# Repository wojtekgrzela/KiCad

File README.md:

# KiCad

My PCB projects in KiCad
 - BodyComputer [DONE]
 - DRL_Driver [DONE]
 - GPS_Adapter [DONE]
 - Listwa_zasilajaca (Power_rail) [DONE]
 - MOSFET_Rail [DONE]
 - Plytka_Dla_Peryferiow (Peripheral_Board) [DONE]
 
 MY_ELEMENTS - Electric components' symbols and footprints from the Internet.
 
 In case you would like to use any of my projects - please contact me via e-mail: wojtekgrzela@gmail.com

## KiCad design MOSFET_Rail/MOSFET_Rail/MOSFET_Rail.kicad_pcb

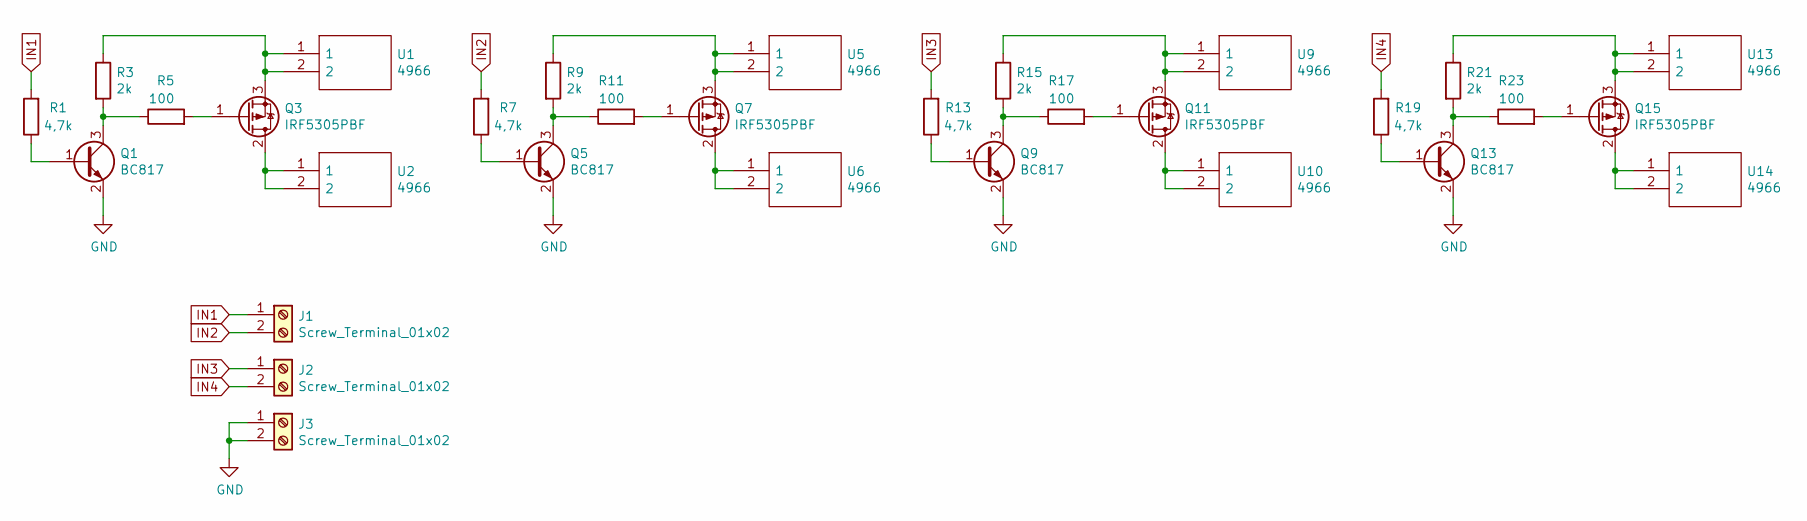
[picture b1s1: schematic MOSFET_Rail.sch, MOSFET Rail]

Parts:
J1, J2, J3: Screw_Terminal_01x02; SHDR2W99P0X500_1X2_1000X760X1000P
Q1, Q5, Q9, Q13: BC817; SOT-23
Q3, Q7, Q11, Q15: IRF5305PBF; TO-220-3_Vertical
R1, R7, R13, R19: 4,7k; R_0805_2012Metric
R3, R9, R15, R21: 2k; R_0805_2012Metric
R5, R11, R17, R23: 100; R_0805_2012Metric
U1, U2, U5, U6, U9, U10, U13, U14: 4966; Mouser Part Number 534-4966

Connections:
GND: J3.1, J3.2, Q1.2 (E), Q5.2 (E), Q9.2 (E), Q13.2 (E)
IN1: J1.1, R1.2
IN2: J1.2, R7.2
IN3: J2.1, R13.2
IN4: J2.2, R19.2
unnamed: Q1.1 (B), R1.1
unnamed: Q1.3 (C), R3.2, R5.1
unnamed: Q3.1 (G), R5.2
unnamed: Q3.2 (D), U2.1, U2.2
unnamed: Q3.3 (S), R3.1, U1.1, U1.2
unnamed: Q5.1 (B), R7.1
unnamed: Q5.3 (C), R9.2, R11.1
unnamed: Q7.1 (G), R11.2
unnamed: Q7.2 (D), U6.1, U6.2
unnamed: Q7.3 (S), R9.1, U5.1, U5.2
unnamed: Q9.1 (B), R13.1
unnamed: Q9.3 (C), R15.2, R17.1
unnamed: Q11.1 (G), R17.2
unnamed: Q11.2 (D), U10.1, U10.2
unnamed: Q11.3 (S), R15.1, U9.1, U9.2
unnamed: Q13.1 (B), R19.1
unnamed: Q13.3 (C), R21.2, R23.1
unnamed: Q15.1 (G), R23.2
unnamed: Q15.2 (D), U14.1, U14.2
unnamed: Q15.3 (S), R21.1, U13.1, U13.2

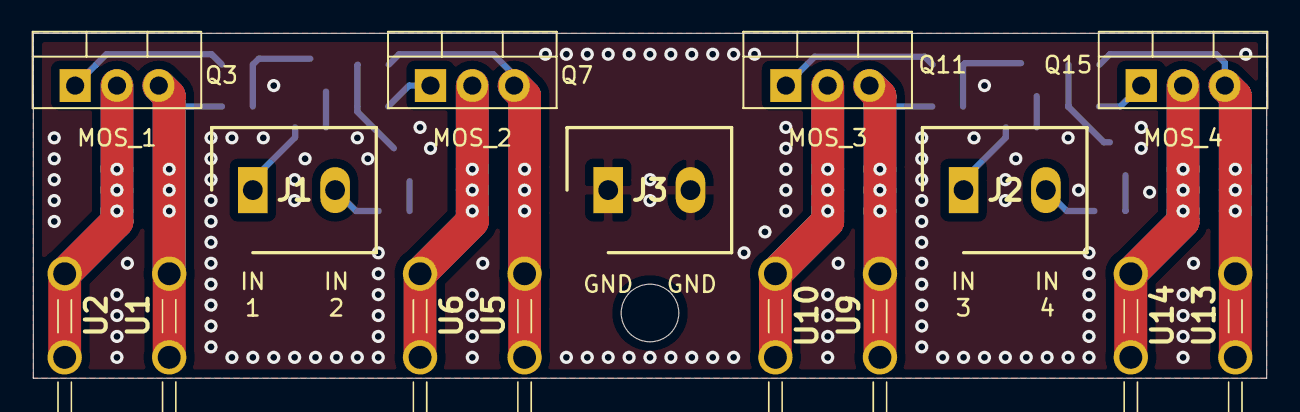
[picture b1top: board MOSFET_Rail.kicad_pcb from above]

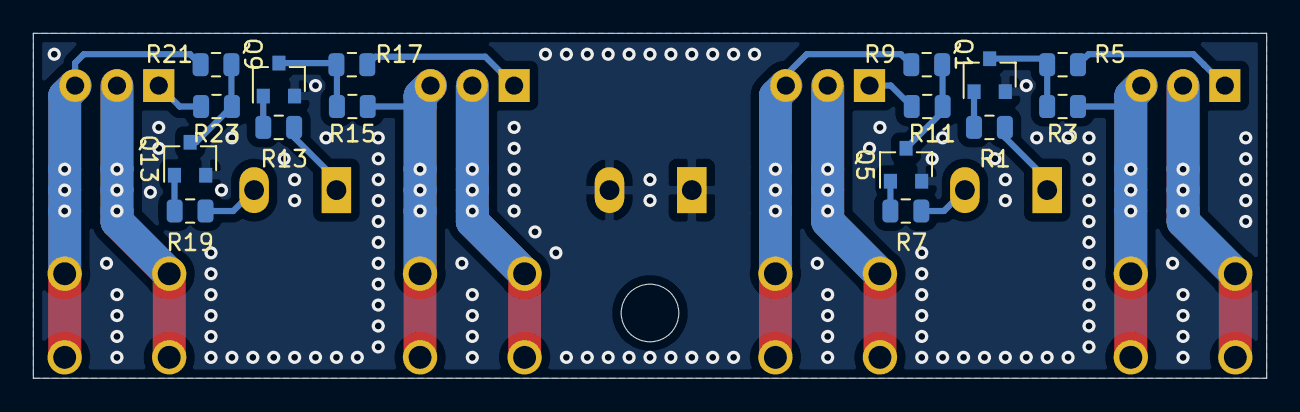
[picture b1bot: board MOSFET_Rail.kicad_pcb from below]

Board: 2 copper layers, 74.9 x 21.0 mm, 31 parts (16 on the bottom side), 25 nets.

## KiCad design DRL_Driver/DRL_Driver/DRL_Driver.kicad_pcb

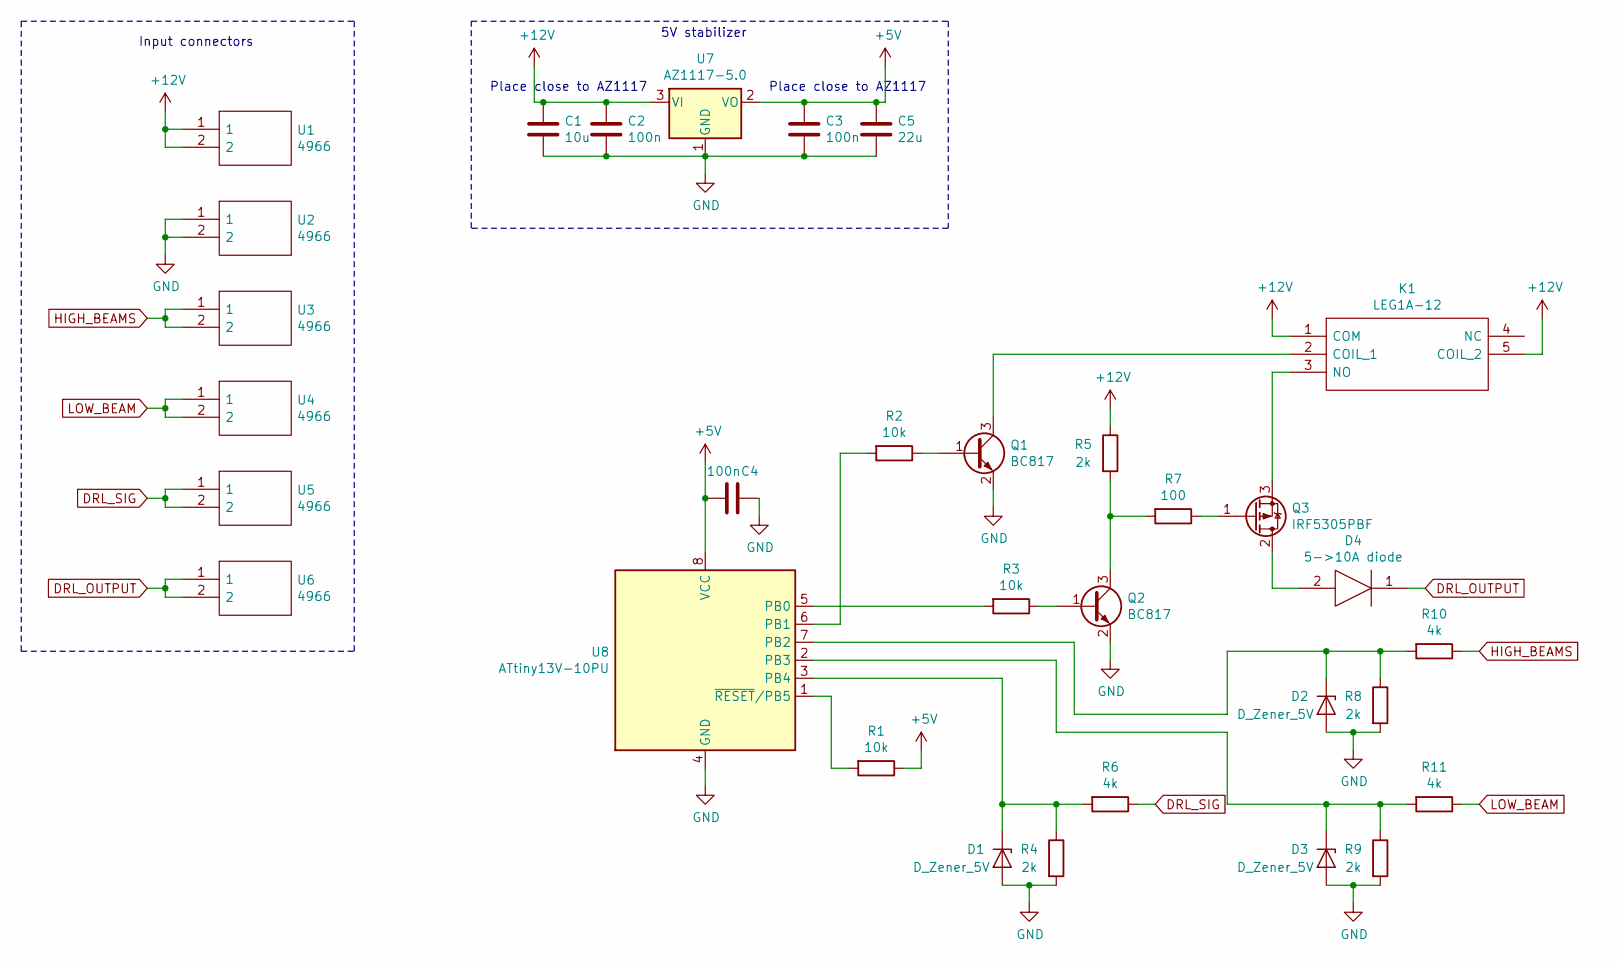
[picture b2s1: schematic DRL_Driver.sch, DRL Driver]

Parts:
C1: 10u; C_1206_3216Metric
C2, C3, C4: 100n; C_0805_2012Metric
C5: 22u; C_0805_2012Metric
D1, D2, D3: D_Zener_5V; D_SOD-323_HandSoldering
D4: 5->10A diode; DIOAD4445W127L889D889; Manufacturer_Part_Number NTE5817HC
K1: LEG1A-12; AZ943; Manufacturer_Part_Number AZ943–1CH–5D
Q1, Q2: BC817; SOT-23
Q3: IRF5305PBF; TO-220-3_Vertical
R1, R2, R3: 10k; R_0805_2012Metric
R4, R5, R8, R9: 2k; R_0805_2012Metric
R6, R10, R11: 4k; R_0805_2012Metric
R7: 100; R_0805_2012Metric
U1, U2, U3, U4, U5, U6: 4966; Mouser Part Number 534-4966
U7: AZ1117-5.0; SOT-223-3_TabPin2
U8: ATtiny13V-10PU; DIP-8_W7.62mm

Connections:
+5V: C3.1, C4.1, C5.1, R1.1, U7.2 (VO), U8.8 (VCC)
+12V: C1.1, C2.1, K1.1 (COM), K1.5 (COIL_2), R5.1, U1.1, U1.2, U7.3 (VI)
DRL_OUTPUT: D4.1, U6.1, U6.2
DRL_SIG: R6.1, U5.1, U5.2
GND: C1.2, C2.2, C3.2, C4.2, C5.2, D1.2 (A), D2.2 (A), D3.2 (A), Q1.2 (E), Q2.2 (E), R4.2, R8.2, R9.2, U2.1, U2.2, U7.1 (GND), U8.4 (GND)
HIGH_BEAMS: R10.1, U3.1, U3.2
LOW_BEAM: R11.1, U4.1, U4.2
unnamed: D1.1 (K), R4.1, R6.2, U8.3 (PB4)
unnamed: D2.1 (K), R8.1, R10.2, U8.7 (PB2)
unnamed: D3.1 (K), R9.1, R11.2, U8.2 (PB3)
unnamed: D4.2, Q3.2 (D)
unnamed: K1.2 (COIL_1), Q1.3 (C)
unnamed: K1.3 (NO), Q3.3 (S)
unnamed: Q1.1 (B), R2.1
unnamed: Q2.1 (B), R3.1
unnamed: Q2.3 (C), R5.2, R7.2
unnamed: Q3.1 (G), R7.1
unnamed: R1.2, U8.1 (~RESET~/PB5)
unnamed: R2.2, U8.6 (PB1)
unnamed: R3.2, U8.5 (PB0)

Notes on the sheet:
Place close to AZ1117
Input connectors
5V stabilizer

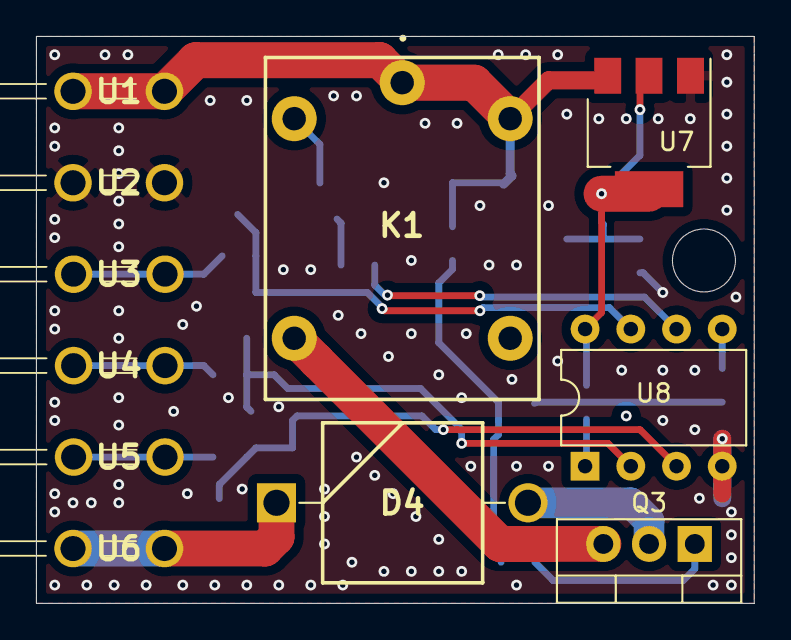
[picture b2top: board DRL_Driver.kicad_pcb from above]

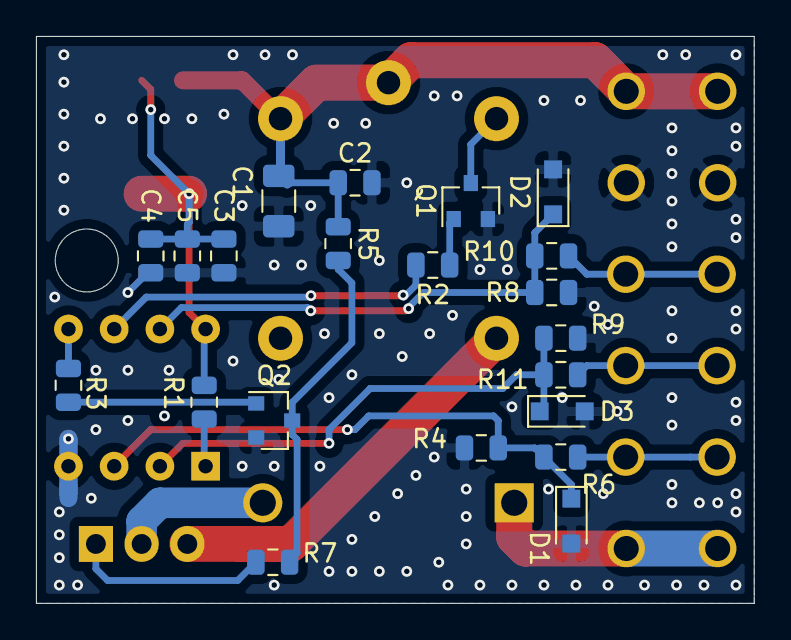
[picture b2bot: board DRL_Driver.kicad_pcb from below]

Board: 2 copper layers, 39.9 x 31.5 mm, 32 parts (21 on the bottom side), 20 nets.

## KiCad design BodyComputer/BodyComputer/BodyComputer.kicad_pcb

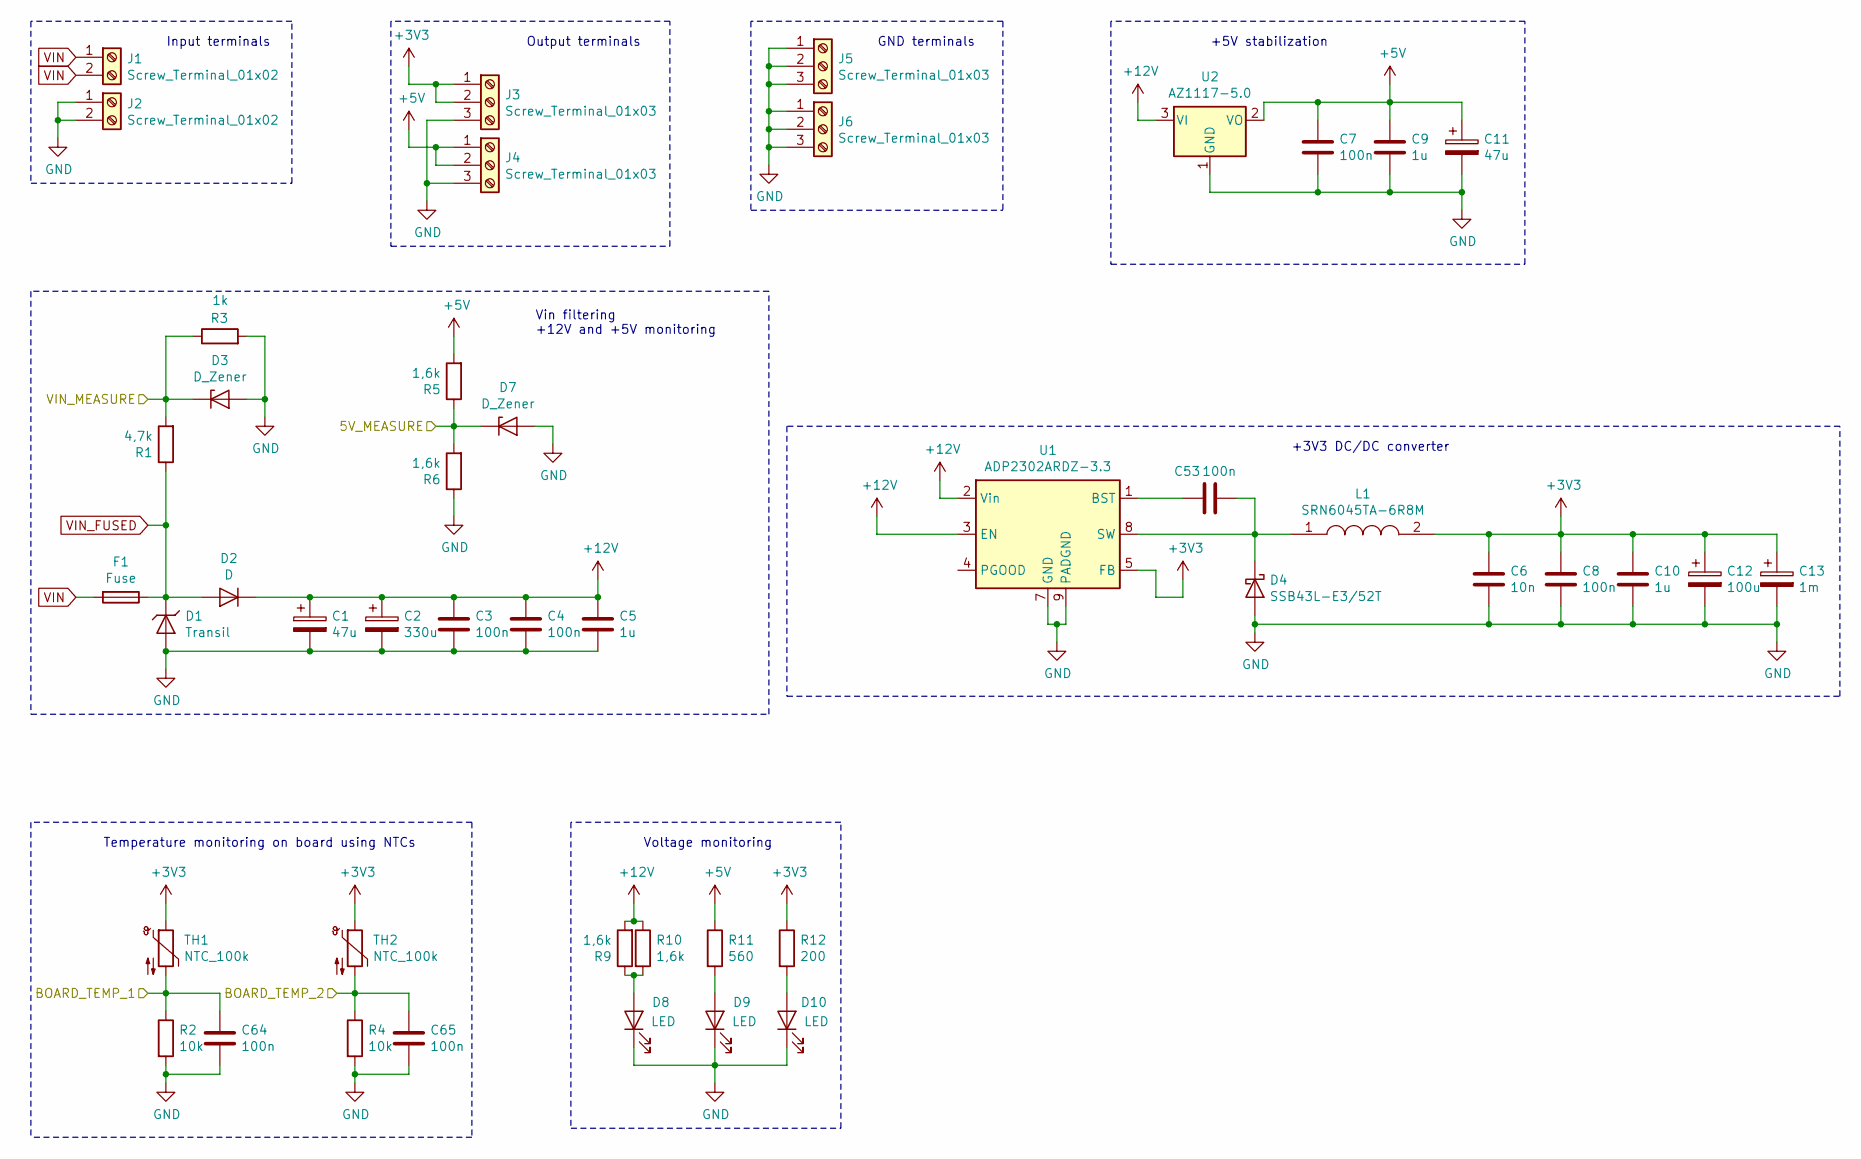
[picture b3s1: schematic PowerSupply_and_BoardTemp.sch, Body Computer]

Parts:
C1, C11: 47u; CP_Elec_6.3x9.9
C2: 330u; CP_Elec_10x12.5
C3, C4, C7, C8, C53, C64, C65: 100n; C_0603_1608Metric
C5, C9, C10: 1u; C_0603_1608Metric
C6: 10n; C_0603_1608Metric
C12: 100u; CP_Elec_6.3x9.9
C13: 1m; CP_Elec_10x12.5
D1: Transil; D_SMB
D2: D; D_SMC
D3, D7: D_Zener; D_SOD-323_HandSoldering
D4: SSB43L-E3/52T; D_SMB
D8, D9, D10: LED; D_0603_1608Metric_Pad1.05x0.95mm_HandSolder
F1: Fuse; FuseHolder22mm
J1, J2: Screw_Terminal_01x02; SHDR2W99P0X500_1X2_1000X760X1000P
J3, J4, J5, J6: Screw_Terminal_01x03; SHDR3W95P0X500_1X3_1620X900X1280P
L1: SRN6045TA-6R8M; Mouser Part Number 652-SRN6045TA-4R7M
R1: 4,7k; R_0603_1608Metric
R2, R4: 10k; R_0603_1608Metric
R3: 1k; R_0603_1608Metric
R5, R6, R9, R10: 1,6k; R_0603_1608Metric
R11: 560; R_0603_1608Metric
R12: 200; R_0603_1608Metric
TH1, TH2: NTC_100k; R_0402_1005Metric
U1: ADP2302ARDZ-3.3; SOIC-8-1EP_3.9x4.9mm_P1.27mm_EP2.29x3mm
U2: AZ1117-5.0; SOT-223-3_TabPin2

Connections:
+3V3: C6.1, C8.1, C10.1, C12.1, C13.1, J3.1, J3.2, L1.2, R12.1, TH1.1, TH2.1, U1.5 (FB); also elsewhere on the board
+5V: C7.1, C9.1, C11.1, J4.1, J4.2, R5.2, R11.1, U2.2 (VO); also elsewhere on the board
+12V: C1.1, C2.1, C3.1, C4.1, C5.1, D2.1 (K), R9.2, R10.1, U1.2 (Vin), U1.3 (EN), U2.3 (VI)
/MCU/ADC_IN10: D3.1 (K), R1.2, R3.1; also elsewhere on the board
/MCU/ADC_IN12: C64.1, R2.1, TH1.2; also elsewhere on the board
/MCU/ADC_IN13: C65.1, R4.1, TH2.2; also elsewhere on the board
/PowerSupply_and_BoardTemp/5V_MEASURE: D7.1 (K), R5.1, R6.2; also elsewhere on the board
GND: C1.2, C2.2, C3.2, C4.2, C5.2, C6.2, C7.2, C8.2, C9.2, C10.2, C11.2, C12.2, C13.2, C64.2, C65.2, D1.2 (A), D3.2 (A), D4.2 (A), D7.2 (A), D8.1 (K), D9.1 (K), D10.1 (K), J2.1, J2.2, J3.3, J4.3, J5.1, J5.2, J5.3, J6.1, J6.2, J6.3, R2.2, R3.2, R4.2, R6.1, U1.7 (GND), U1.9 (PADGND), U2.1 (GND); also elsewhere on the board
unnamed: C53.1, U1.1 (BST)
unnamed: C53.2, D4.1 (K), L1.1, U1.8 (SW)
unnamed: D8.2 (A), R9.1, R10.2
unnamed: D9.2 (A), R11.2
unnamed: D10.2 (A), R12.2
VIN: F1.2, J1.1, J1.2; also elsewhere on the board
VIN_FUSED: D1.1 (K), D2.2 (A), F1.1, R1.1; also elsewhere on the board

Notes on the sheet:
Temperature monitoring on board using NTCs
Vin filtering +12V and +5V monitoring
+5V stabilization
Input terminals
Output terminals
GND terminals
Voltage monitoring
+3V3 DC/DC converter

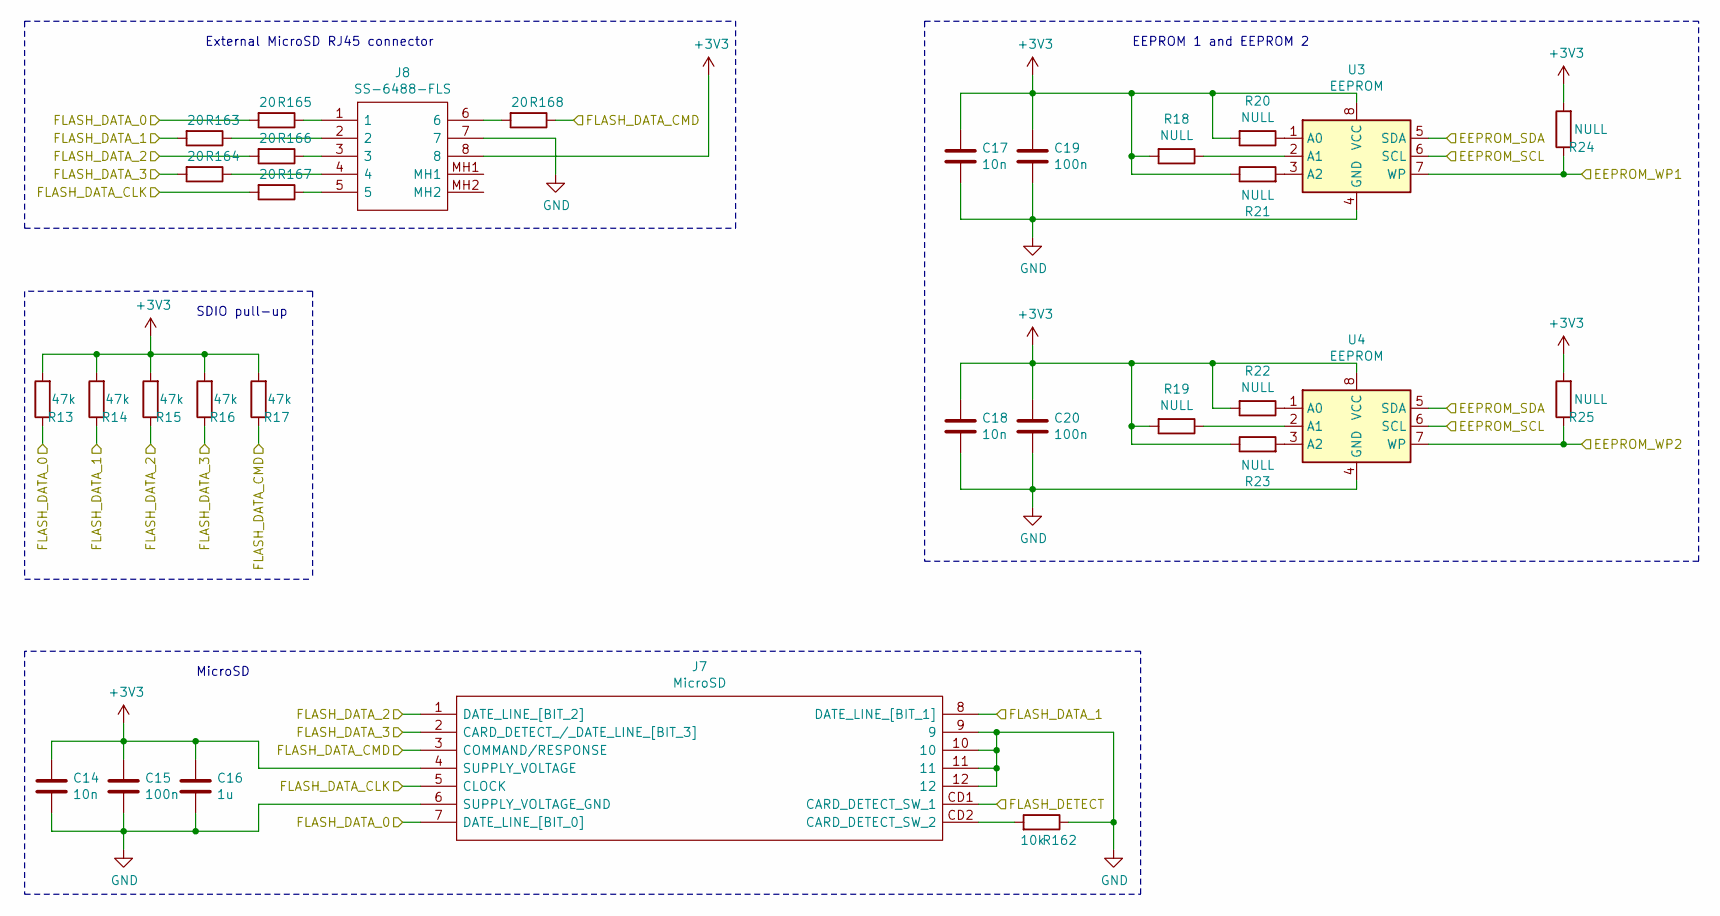
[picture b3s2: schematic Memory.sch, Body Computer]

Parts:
C14, C17, C18: 10n; C_0603_1608Metric
C15, C19, C20: 100n; C_0603_1608Metric
C16: 1u; C_0603_1608Metric
J7: MicroSD; 1140084168; Mouser Part Number 523-114-00841-68
J8: SS-6488-FLS; SS6488FLS; Mouser Part Number 530-SS-6488-FLS
R13, R14, R15, R16, R17: 47k; R_0603_1608Metric
R18, R19, R20, R21, R22, R23, R24, R25: NULL; R_0603_1608Metric
R162: 10k; R_0603_1608Metric
R163, R164, R165, R166, R167, R168: 20; R_0603_1608Metric
U3, U4: EEPROM; SO-8_3.9x4.9mm_P1.27mm

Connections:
+3V3: C14.1, C15.1, C16.1, C17.1, C18.1, C19.1, C20.1, J7.4 (SUPPLY_VOLTAGE), J8.8, R13.2, R14.2, R15.2, R16.2, R17.2, R18.2, R19.2, R20.2, R21.1, R22.2, R23.1, R24.2, R25.2, U3.8 (VCC), U4.8 (VCC); also elsewhere on the board
/MCU/Diag_LED_1: J7.CD1 (CARD_DETECT_SW_1); also elsewhere on the board
/MCU/EEPROM_WP1: R24.1, U3.7 (WP); also elsewhere on the board
/MCU/EEPROM_WP2: R25.1, U4.7 (WP); also elsewhere on the board
/Memory/EEPROM_SCL: U3.6 (SCL), U4.6 (SCL); also elsewhere on the board
/Memory/EEPROM_SDA: U3.5 (SDA), U4.5 (SDA); also elsewhere on the board
/Memory/FLASH_DATA_0: J7.7 (DATE_LINE_[BIT_0]), R13.1, R165.2; also elsewhere on the board
/Memory/FLASH_DATA_1: J7.8 (DATE_LINE_[BIT_1]), R14.1, R163.2; also elsewhere on the board
/Memory/FLASH_DATA_2: J7.1 (DATE_LINE_[BIT_2]), R15.1, R166.2; also elsewhere on the board
/Memory/FLASH_DATA_3: J7.2 (CARD_DETECT_/_DATE_LINE_[BIT_3]), R16.1, R164.2; also elsewhere on the board
/Memory/FLASH_DATA_CLK: J7.5 (CLOCK), R167.2; also elsewhere on the board
/Memory/FLASH_DATA_CMD: J7.3 (COMMAND/RESPONSE), R17.1, R168.1; also elsewhere on the board
GND: C14.2, C15.2, C16.2, C17.2, C18.2, C19.2, C20.2, J7.6 (SUPPLY_VOLTAGE_GND), J7.9, J7.10, J7.11, J7.12, J8.7, R162.1, U3.4 (GND), U4.4 (GND); also elsewhere on the board
unnamed: J7.CD2 (CARD_DETECT_SW_2), R162.2
unnamed: J8.1, R165.1
unnamed: J8.2, R163.1
unnamed: J8.3, R166.1
unnamed: J8.4, R164.1
unnamed: J8.5, R167.1
unnamed: J8.6, R168.2
unnamed: R18.1, U3.2 (A1)
unnamed: R19.1, U4.2 (A1)
unnamed: R20.1, U3.1 (A0)
unnamed: R21.2, U3.3 (A2)
unnamed: R22.1, U4.1 (A0)
unnamed: R23.2, U4.3 (A2)

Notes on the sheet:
SDIO pull-up
External MicroSD RJ45 connector
EEPROM 1 and EEPROM 2
MicroSD

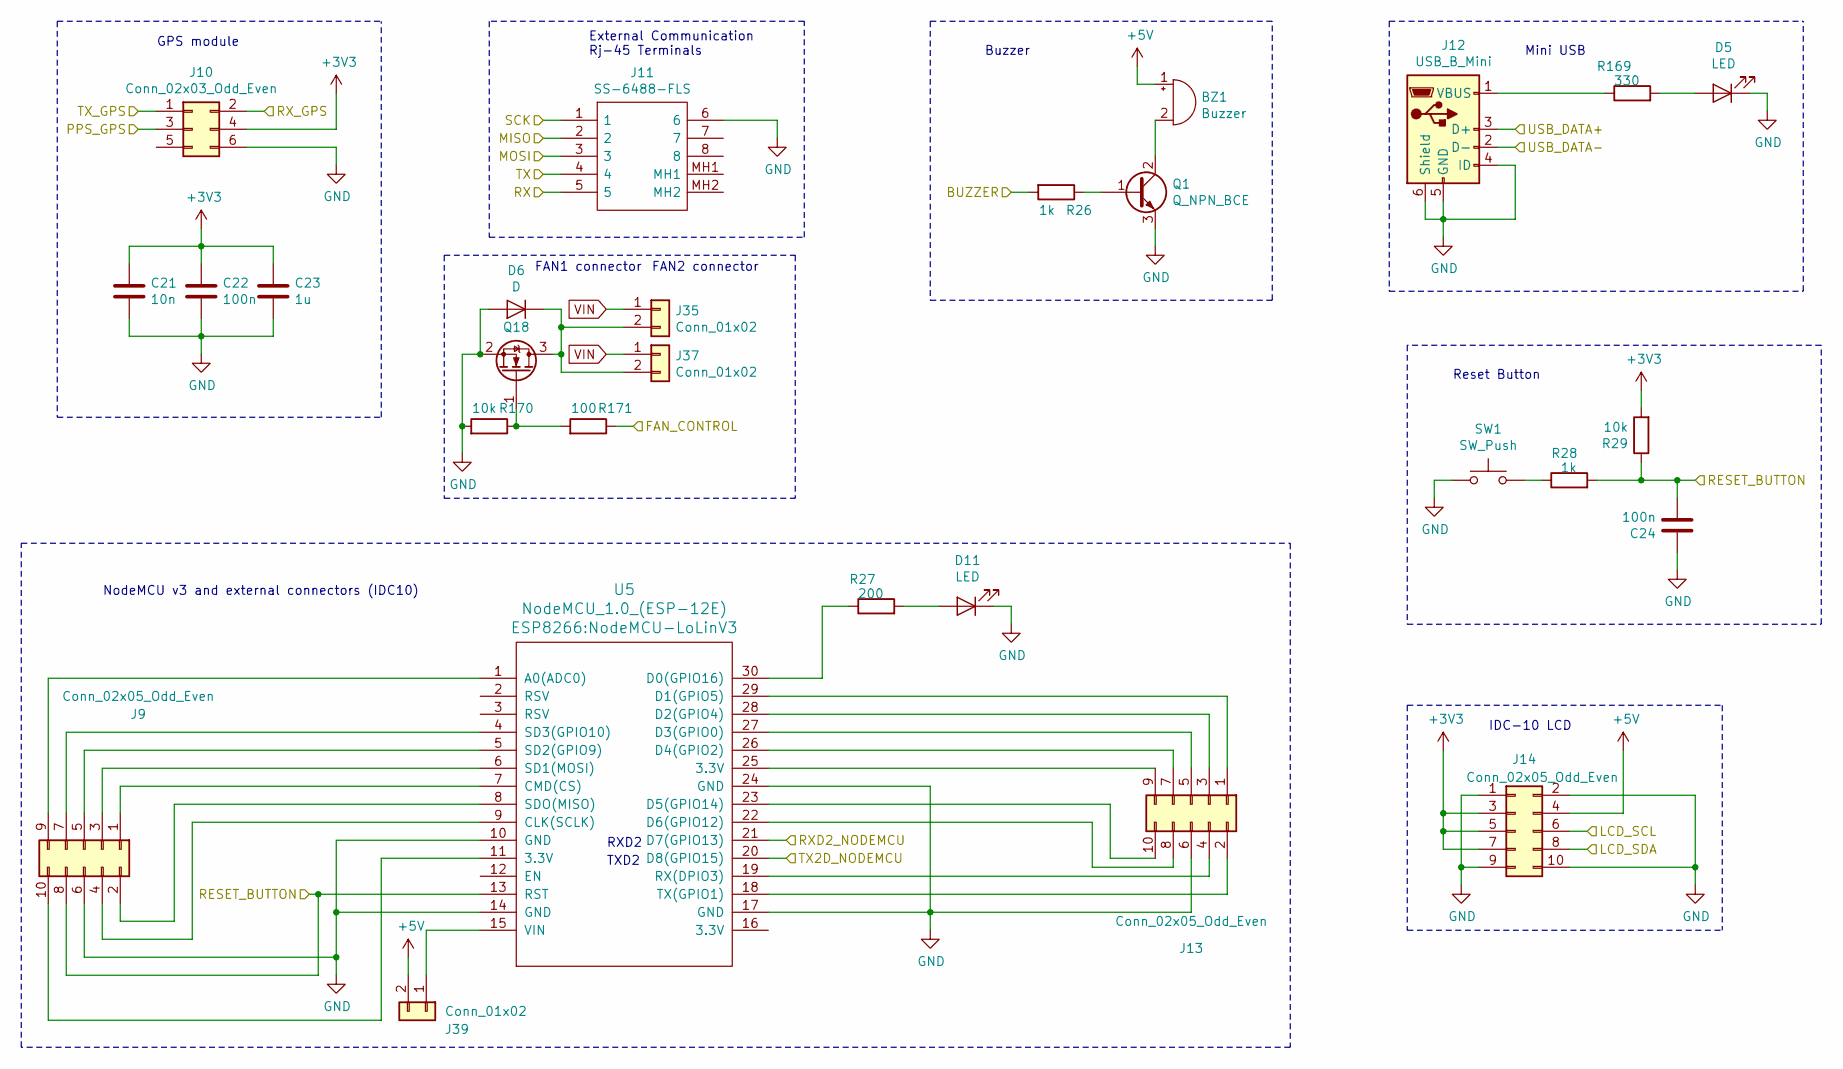
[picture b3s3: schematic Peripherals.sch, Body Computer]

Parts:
BZ1: Buzzer; Buzzer_12x9.5RM7.6
C21: 10n; C_0603_1608Metric
C22, C24: 100n; C_0603_1608Metric
C23: 1u; C_0603_1608Metric
D5, D11: LED; D_0603_1608Metric_Pad1.05x0.95mm_HandSolder
D6: D; D_SMA
J9, J13, J14: Conn_02x05_Odd_Even; IDC-Header_2x05_P2.54mm_Vertical
J10: Conn_02x03_Odd_Even; IDC-Header_2x03_P2.54mm_Vertical
J11: SS-6488-FLS; SS6488FLS; Mouser Part Number 530-SS-6488-FLS
J12: USB_B_Mini; USB_Mini-B_Wuerth_65100516121_Horizontal
J35, J37, J39: Conn_01x02; PinSocket_1x02_P2.54mm_Vertical
Q1: Q_NPN_BCE; SOT-23
Q18: IRLML2060; SOT-23
R26, R28: 1k; R_0603_1608Metric
R27: 200; R_0603_1608Metric
R29, R170: 10k; R_0603_1608Metric
R169: 330; R_0603_1608Metric
R171: 100; R_0603_1608Metric
SW1: SW_Push; SW_PUSH_6mm
U5: NodeMCU_1.0_(ESP-12E); NodeMCU-LoLinV3

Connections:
+3V3: C21.1, C22.1, C23.1, J10.4, J14.3, J14.5, J14.7, R29.2; also elsewhere on the board
+5V: BZ1.1 (-), J14.4, J39.2; also elsewhere on the board
/MCU/Diag_LED_8: R171.1; also elsewhere on the board
/MCU/I2C2_SCL: J14.6; also elsewhere on the board
/MCU/I2C2_SDA: J14.8; also elsewhere on the board
/MCU/NRST: C24.2, J9.8, R28.2, R29.1, U5.13 (RST); also elsewhere on the board
/Peripherals/BUZZER: R26.2; also elsewhere on the board
/Peripherals/MISO: J11.2; also elsewhere on the board
/Peripherals/MOSI: J11.3; also elsewhere on the board
/Peripherals/PPS_GPS: J10.3; also elsewhere on the board
/Peripherals/RX: J11.5; also elsewhere on the board
/Peripherals/RXD2_NODEMCU: U5.21 (D7(GPIO13)); also elsewhere on the board
/Peripherals/RX_GPS: J10.2; also elsewhere on the board
/Peripherals/SCK: J11.1; also elsewhere on the board
/Peripherals/TX: J11.4; also elsewhere on the board
/Peripherals/TX2D_NODEMCU: U5.20 (D8(GPIO15)); also elsewhere on the board
/Peripherals/TX_GPS: J10.1; also elsewhere on the board
/Peripherals/USB_DATA+: J12.3 (D+); also elsewhere on the board
/Peripherals/USB_DATA-: J12.2 (D-); also elsewhere on the board
GND: C21.2, C22.2, C23.2, C24.1, D5.1 (K), D6.2 (A), D11.1 (K), J9.6, J10.6, J11.6, J12.4 (ID), J12.5 (GND), J12.6 (Shield), J13.6, J14.1, J14.2, J14.9, J14.10, Q1.3 (E), Q18.2 (S), R170.2, SW1.1, U5.10 (GND), U5.14 (GND), U5.17 (GND), U5.24 (GND); also elsewhere on the board
unnamed: BZ1.2 (+), Q1.2 (C)
unnamed: D5.2 (A), R169.2
unnamed: D6.1 (K), J35.2, J37.2, Q18.3 (D)
unnamed: D11.2 (A), R27.2
unnamed: J9.1, U5.7 (CMD(CS))
unnamed: J9.2, U5.8 (SDO(MISO))
unnamed: J9.3, U5.6 (SD1(MOSI))
unnamed: J9.4, U5.9 (CLK(SCLK))
unnamed: J9.5, U5.5 (SD2(GPIO9))
unnamed: J9.7, U5.4 (SD3(GPIO10))
unnamed: J9.9, U5.1 (A0(ADC0))
unnamed: J9.10, U5.11 (3.3V)
unnamed: J12.1 (VBUS), R169.1
unnamed: J13.1, U5.29 (D1(GPIO5))
unnamed: J13.2, U5.18 (TX(GPIO1))
unnamed: J13.3, U5.28 (D2(GPIO4))
unnamed: J13.4, U5.19 (RX(DPIO3))
unnamed: J13.5, U5.27 (D3(GPIO0))
unnamed: J13.7, U5.26 (D4(GPIO2))
unnamed: J13.8, U5.22 (D6(GPIO12))
unnamed: J13.9, U5.25 (3.3V)
unnamed: J13.10, U5.23 (D5(GPIO14))
unnamed: J39.1, U5.15 (VIN)
unnamed: Q1.1 (B), R26.1
unnamed: Q18.1 (G), R170.1, R171.2
unnamed: R27.1, U5.30 (D0(GPIO16))
unnamed: R28.1, SW1.2
VIN: J35.1, J37.1; also elsewhere on the board

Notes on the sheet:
GPS module
External Communication Rj-45 Terminals
RXD2
TXD2
Buzzer
Mini USB
IDC-10 LCD
Reset Button
NodeMCU v3 and external connectors (IDC10)
FAN1 connector
FAN2 connector

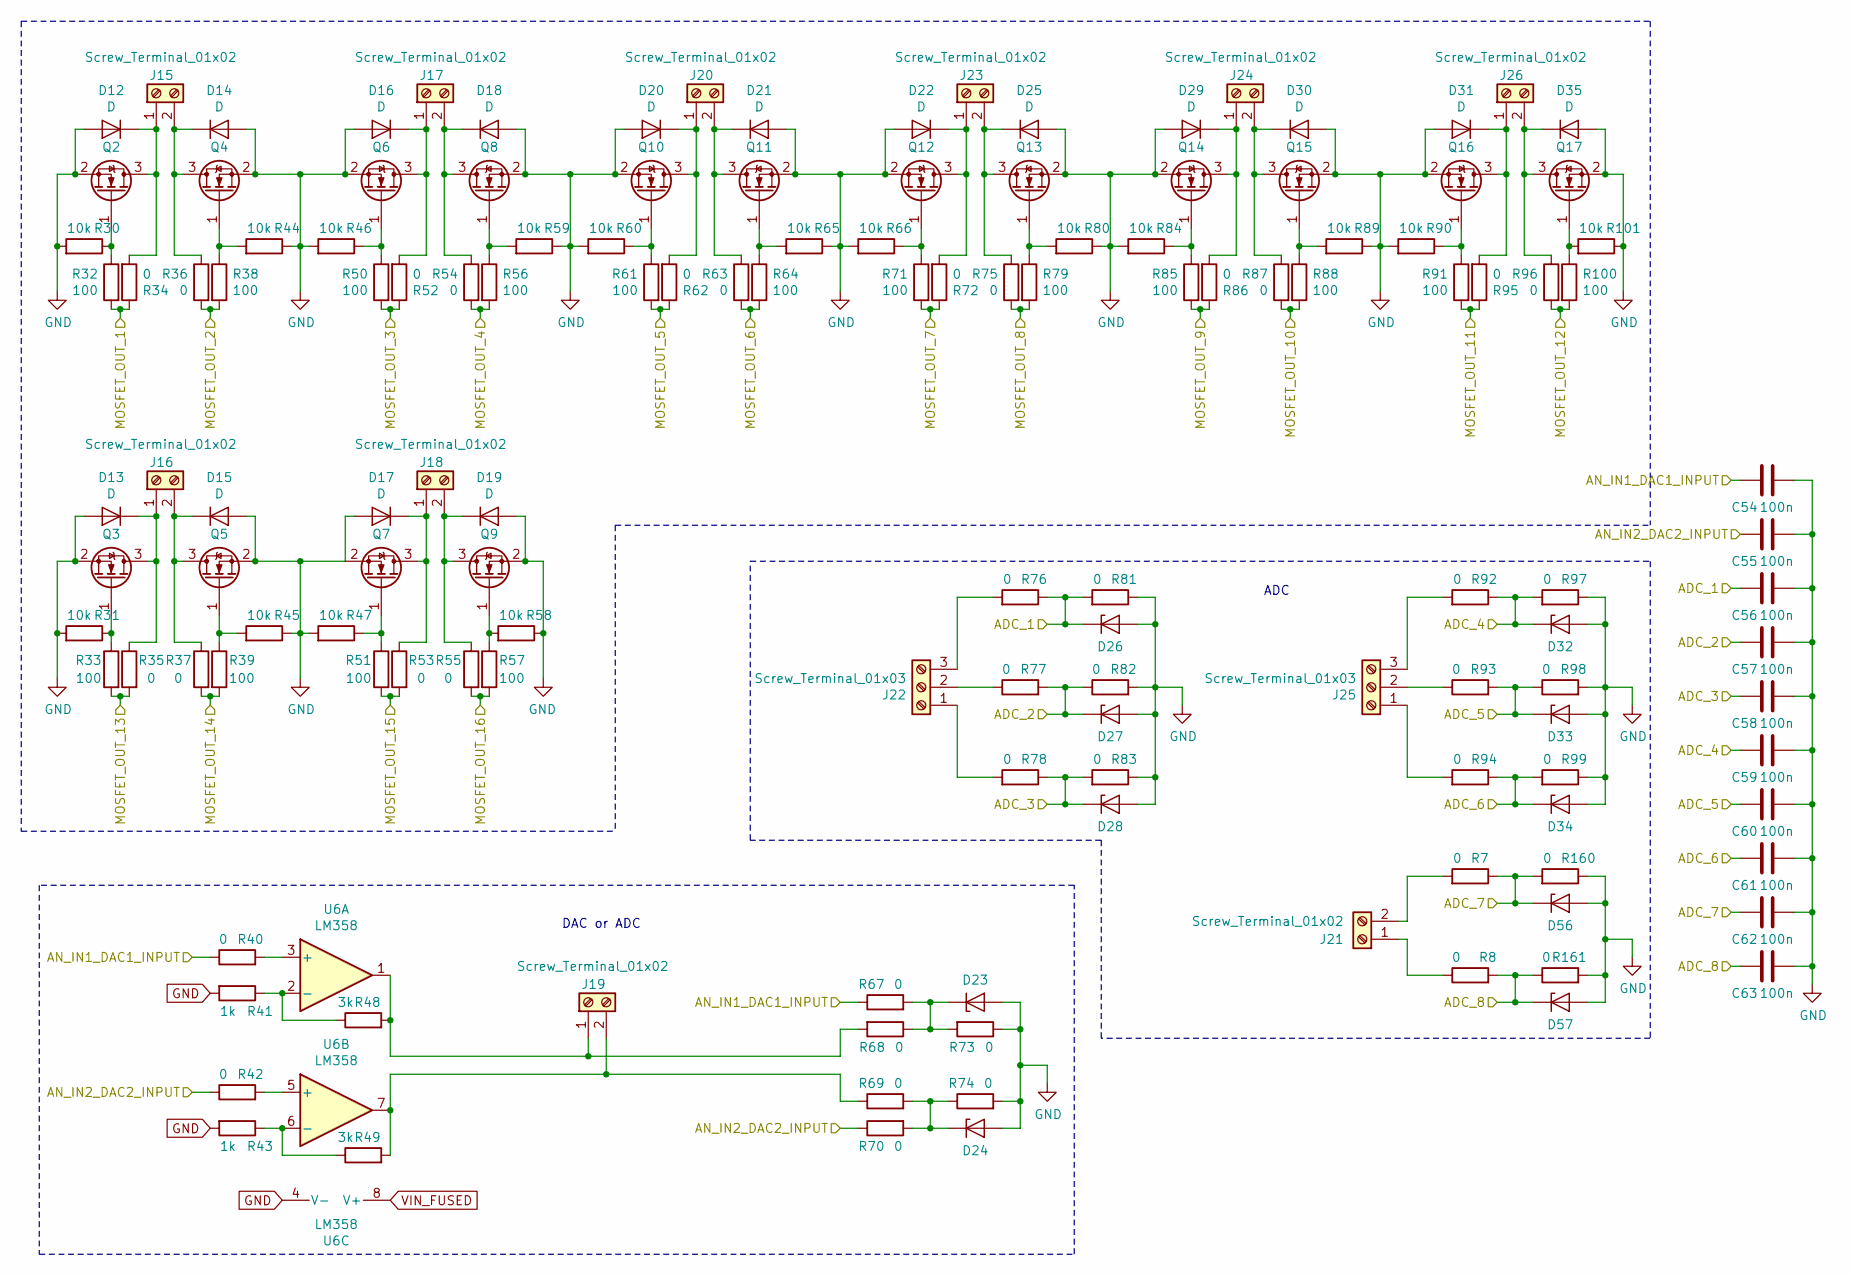
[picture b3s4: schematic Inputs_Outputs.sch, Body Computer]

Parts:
C54, C55, C56, C57, C58, C59, C60, C61, C62, C63: 100n; C_0603_1608Metric
D12, D13, D14, D15, D16, D17, D18, D19, D20, D21, D22, D25, D29, D30, D31, D35: D; D_SMA
D23, D24, D26, D27, D28, D32, D33, D34, D56, D57: D_Zener; D_SOD-323_HandSoldering
J15, J16, J17, J18, J19, J20, J21, J23, J24, J26: Screw_Terminal_01x02; SHDR2W99P0X500_1X2_1000X760X1000P
J22, J25: Screw_Terminal_01x03; SHDR3W95P0X500_1X3_1620X900X1280P
Q2, Q3, Q4, Q5, Q6, Q7, Q8, Q9, Q10, Q11, Q12, Q13, Q14, Q15, Q16, Q17: IRLML2060; SOT-23
R7, R8, R34, R35, R36, R37, R40, R42, R52, R53, R54, R55, R62, R63, R67, R68, R69, R70, R72, R73, R74, R75, R76, R77, R78, R81, R82, R83, R86, R87, R92, R93, R94, R95, R96, R97, R98, R99, R160, R161: 0; R_0603_1608Metric
R30, R31, R44, R45, R46, R47, R58, R59, R60, R65, R66, R80, R84, R89, R90, R101: 10k; R_0603_1608Metric
R32, R33, R38, R39, R50, R51, R56, R57, R61, R64, R71, R79, R85, R88, R91, R100: 100; R_0603_1608Metric
R41, R43: 1k; R_0603_1608Metric
R48, R49: 3k; R_0603_1608Metric
U6: LM358

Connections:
/Inputs_Outputs/ADC_1: C56.2, D26.1 (K), R76.1, R81.2; also elsewhere on the board
/Inputs_Outputs/ADC_2: C57.2, D27.1 (K), R77.2, R82.1; also elsewhere on the board
/Inputs_Outputs/ADC_3: C58.2, D28.1 (K), R78.1, R83.2; also elsewhere on the board
/Inputs_Outputs/ADC_4: C59.2, D32.1 (K), R92.1, R97.2; also elsewhere on the board
/Inputs_Outputs/ADC_5: C60.2, D33.1 (K), R93.2, R98.1; also elsewhere on the board
/Inputs_Outputs/ADC_6: C61.2, D34.1 (K), R94.1, R99.2; also elsewhere on the board
/Inputs_Outputs/ADC_7: C62.2, D56.1 (K), R7.1, R160.2; also elsewhere on the board
/Inputs_Outputs/ADC_8: C63.2, D57.1 (K), R8.2, R161.1; also elsewhere on the board
/Inputs_Outputs/AN_IN1_DAC1_INPUT: C54.2, R40.1, R67.1; also elsewhere on the board
/Inputs_Outputs/AN_IN2_DAC2_INPUT: C55.2, R42.1, R70.1; also elsewhere on the board
/Inputs_Outputs/MOSFET_OUT_1: R32.2, R34.1; also elsewhere on the board
/Inputs_Outputs/MOSFET_OUT_2: R36.2, R38.2; also elsewhere on the board
/Inputs_Outputs/MOSFET_OUT_3: R50.2, R52.1; also elsewhere on the board
/Inputs_Outputs/MOSFET_OUT_4: R54.2, R56.2; also elsewhere on the board
/Inputs_Outputs/MOSFET_OUT_5: R61.2, R62.1; also elsewhere on the board
/Inputs_Outputs/MOSFET_OUT_6: R63.2, R64.2; also elsewhere on the board
/Inputs_Outputs/MOSFET_OUT_7: R71.2, R72.1; also elsewhere on the board
/Inputs_Outputs/MOSFET_OUT_8: R75.2, R79.2; also elsewhere on the board
/Inputs_Outputs/MOSFET_OUT_9: R85.2, R86.1; also elsewhere on the board
/Inputs_Outputs/MOSFET_OUT_10: R87.2, R88.2; also elsewhere on the board
/Inputs_Outputs/MOSFET_OUT_11: R91.2, R95.1; also elsewhere on the board
/Inputs_Outputs/MOSFET_OUT_12: R96.2, R100.2; also elsewhere on the board
/Inputs_Outputs/MOSFET_OUT_13: R33.2, R35.2; also elsewhere on the board
/Inputs_Outputs/MOSFET_OUT_14: R37.2, R39.2; also elsewhere on the board
/MCU/MOSFET_15: R51.2, R53.2; also elsewhere on the board
/MCU/MOSFET_16: R55.2, R57.2; also elsewhere on the board
GND: C54.1, C55.1, C56.1, C57.1, C58.1, C59.1, C60.1, C61.1, C62.1, C63.1, D12.2 (A), D13.2 (A), D14.2 (A), D15.2 (A), D16.2 (A), D17.2 (A), D18.2 (A), D19.2 (A), D20.2 (A), D21.2 (A), D22.2 (A), D23.2 (A), D24.2 (A), D25.2 (A), D26.2 (A), D27.2 (A), D28.2 (A), D29.2 (A), D30.2 (A), D31.2 (A), D32.2 (A), D33.2 (A), D34.2 (A), D35.2 (A), D56.2 (A), D57.2 (A), Q2.2 (S), Q3.2 (S), Q4.2 (S), Q5.2 (S), Q6.2 (S), Q7.2 (S), Q8.2 (S), Q9.2 (S), Q10.2 (S), Q11.2 (S), Q12.2 (S), Q13.2 (S), Q14.2 (S), Q15.2 (S), Q16.2 (S), Q17.2 (S), R30.2, R31.2, R41.2, R43.2, R44.1, R45.1, R46.2, R47.2, R58.1, R59.1, R60.2, R65.1, R66.2, R73.1, R74.2, R80.1, R81.1, R82.2, R83.1, R84.2, R89.1, R90.2, R97.1, R98.2, R99.1, R101.1, R160.1, R161.2, U6.4 (V-); also elsewhere on the board
unnamed: D12.1 (K), J15.1, Q2.3 (D), R34.2
unnamed: D13.1 (K), J16.1, Q3.3 (D), R35.1
unnamed: D14.1 (K), J15.2, Q4.3 (D), R36.1
unnamed: D15.1 (K), J16.2, Q5.3 (D), R37.1
unnamed: D16.1 (K), J17.1, Q6.3 (D), R52.2
unnamed: D17.1 (K), J18.1, Q7.3 (D), R53.1
unnamed: D18.1 (K), J17.2, Q8.3 (D), R54.1
unnamed: D19.1 (K), J18.2, Q9.3 (D), R55.1
unnamed: D20.1 (K), J20.1, Q10.3 (D), R62.2
unnamed: D21.1 (K), J20.2, Q11.3 (D), R63.1
unnamed: D22.1 (K), J23.1, Q12.3 (D), R72.2
unnamed: D23.1 (K), R67.2, R68.1, R73.2
unnamed: D24.1 (K), R69.2, R70.2, R74.1
unnamed: D25.1 (K), J23.2, Q13.3 (D), R75.1
unnamed: D29.1 (K), J24.1, Q14.3 (D), R86.2
unnamed: D30.1 (K), J24.2, Q15.3 (D), R87.1
unnamed: D31.1 (K), J26.1, Q16.3 (D), R95.2
unnamed: D35.1 (K), J26.2, Q17.3 (D), R96.1
unnamed: J19.1, R48.2, R68.2, U6.1
unnamed: J19.2, R49.2, R69.1, U6.7
unnamed: J21.1, R8.1
unnamed: J21.2, R7.2
unnamed: J22.1, R78.2
unnamed: J22.2, R77.1
unnamed: J22.3, R76.2
unnamed: J25.1, R94.2
unnamed: J25.2, R93.1
unnamed: J25.3, R92.2
unnamed: Q2.1 (G), R30.1, R32.1
unnamed: Q3.1 (G), R31.1, R33.1
unnamed: Q4.1 (G), R38.1, R44.2
unnamed: Q5.1 (G), R39.1, R45.2
unnamed: Q6.1 (G), R46.1, R50.1
unnamed: Q7.1 (G), R47.1, R51.1
unnamed: Q8.1 (G), R56.1, R59.2
unnamed: Q9.1 (G), R57.1, R58.2
unnamed: Q10.1 (G), R60.1, R61.1
unnamed: Q11.1 (G), R64.1, R65.2
unnamed: Q12.1 (G), R66.1, R71.1
unnamed: Q13.1 (G), R79.1, R80.2
unnamed: Q14.1 (G), R84.1, R85.1
unnamed: Q15.1 (G), R88.1, R89.2
unnamed: Q16.1 (G), R90.1, R91.1
unnamed: Q17.1 (G), R100.1, R101.2
unnamed: R40.2, U6.3 (+)
unnamed: R41.1, R48.1, U6.2 (-)
unnamed: R42.2, U6.5 (+)
unnamed: R43.1, R49.1, U6.6 (-)
VIN_FUSED: U6.8 (V+); also elsewhere on the board

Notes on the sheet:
ADC
DAC or ADC
